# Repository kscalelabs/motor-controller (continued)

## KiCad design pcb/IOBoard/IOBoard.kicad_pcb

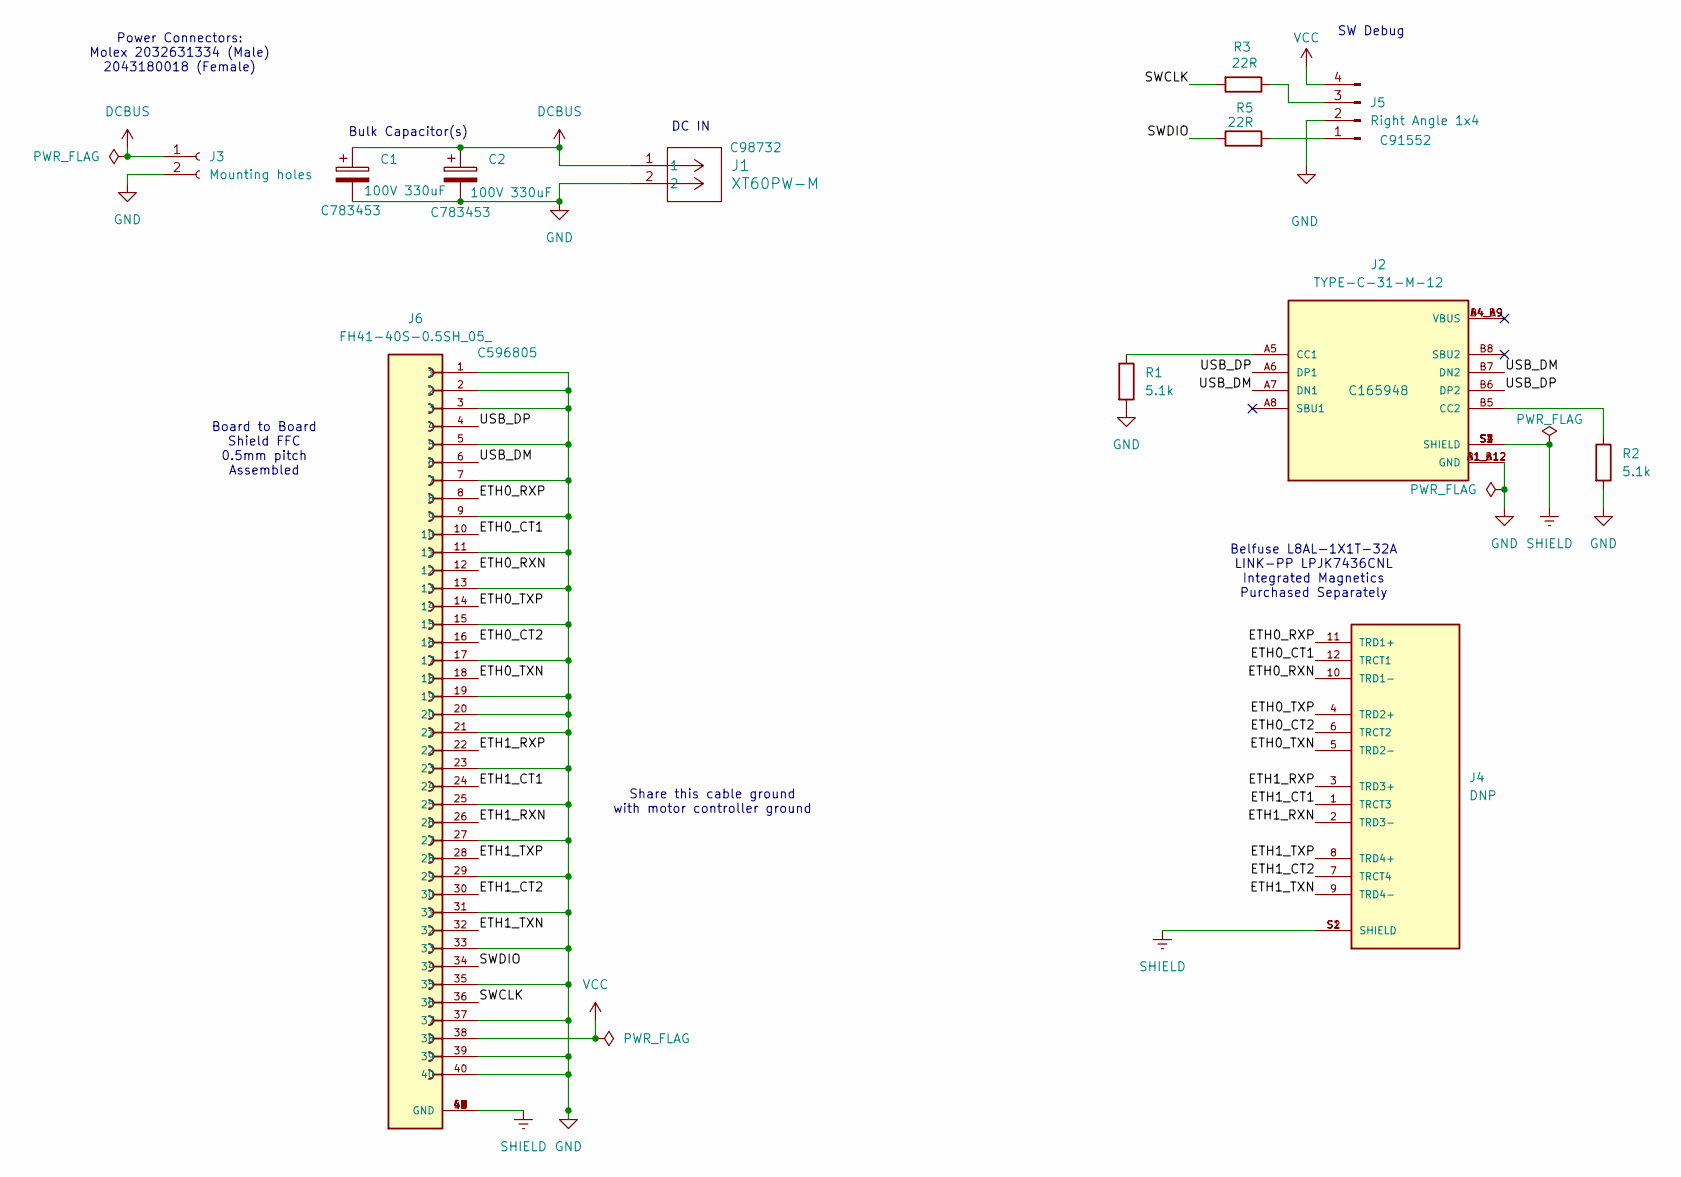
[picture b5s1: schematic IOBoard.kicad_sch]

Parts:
C1, C2: 100V 330uF; CP_Radial_D13.0mm_P5.00mm; LCSC Part Number C783453
J1: XT60PW-M; CONN_XT60PW-M_AMA; LCSC Part Number C98732
J2: TYPE-C-31-M-12; HRO_TYPE-C-31-M-12; PARTREV 2020.12.08; LCSC Part Number C165948
J3: Mounting holes; Dual Post
J4: DNP; BEL_L8AL-1X1T-32A; PARTREV A; LCSC Part Number LINK-PP LPJK7436CNL
J5: Right Angle 1x4; PinHeader_1x04_P2.54mm_Horizontal; LCSC Part Number C91552
J6: FH41-40S-0.5SH_05_; HRS_FH41-40S-0.5SH_05_; PARTREV 18.03.19; LCSC Part Number C596805
R1, R2: 5.1k; R_0603_1608Metric
R3, R5: 22R; R_0603_1608Metric; TOLERANCE ±1%; MANUFACTURER PART NUMBER RC0603FR-0722RL

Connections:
/ETH0_CT1: J4.12 (TRCT1), J6.10
/ETH0_CT2: J4.6 (TRCT2), J6.16
/ETH0_RXN: J4.10 (TRD1-), J6.12
/ETH0_RXP: J4.11 (TRD1+), J6.8
/ETH0_TXN: J4.5 (TRD2-), J6.18
/ETH0_TXP: J4.4 (TRD2+), J6.14
/ETH1_CT1: J4.1 (TRCT3), J6.24
/ETH1_CT2: J4.7 (TRCT4), J6.30
/ETH1_RXN: J4.2 (TRD3-), J6.26
/ETH1_RXP: J4.3 (TRD3+), J6.22
/ETH1_TXN: J4.9 (TRD4-), J6.32
/ETH1_TXP: J4.8 (TRD4+), J6.28
/SWCLK: J6.36, R3.2
/SWDIO: J6.34, R5.1
/USB_DM: J2.A7 (DN1), J2.B7 (DN2), J6.6
/USB_DP: J2.A6 (DP1), J2.B6 (DP2), J6.4
DCBUS: C1.1, C2.1, J1.1, J3.1
GND: C1.2, C2.2, J1.2, J2.A1_B12 (GND), J2.B1_A12 (GND), J3.2, J5.2, J6.1, J6.2, J6.3, J6.5, J6.7, J6.9, J6.11, J6.13, J6.15, J6.17, J6.19, J6.20, J6.21, J6.23, J6.25, J6.27, J6.29, J6.31, J6.33, J6.35, J6.37, J6.39, J6.40, R1.2, R2.2
unnamed: J2.A5 (CC1), R1.1
unnamed: J2.B5 (CC2), R2.1
unnamed: J5.1, R5.2
unnamed: J5.3, R3.1
SHIELD: J2.S1 (SHIELD), J2.S2 (SHIELD), J2.S3 (SHIELD), J2.S4 (SHIELD), J4.S1 (SHIELD), J4.S2 (SHIELD), J6.41 (GND), J6.42 (GND), J6.43 (GND), J6.44 (GND), J6.45 (GND), J6.46 (GND), J6.47 (GND), J6.48 (GND), J6.49 (GND), J6.50 (GND)
VCC: J5.4, J6.38

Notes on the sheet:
Belfuse L8AL-1X1T-32A LINK-PP LPJK7436CNL Integrated Magnetics Purchased Separately
SW Debug
Board to Board Shield FFC 0.5mm pitch Assembled
Share this cable ground with motor controller ground
DC IN
Power Connectors: Molex 2032631334 (Male) 2043180018 (Female)
Bulk Capacitor(s)

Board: 4 copper layers, 12 parts (0 on the bottom side), 24 nets, no tracks yet.

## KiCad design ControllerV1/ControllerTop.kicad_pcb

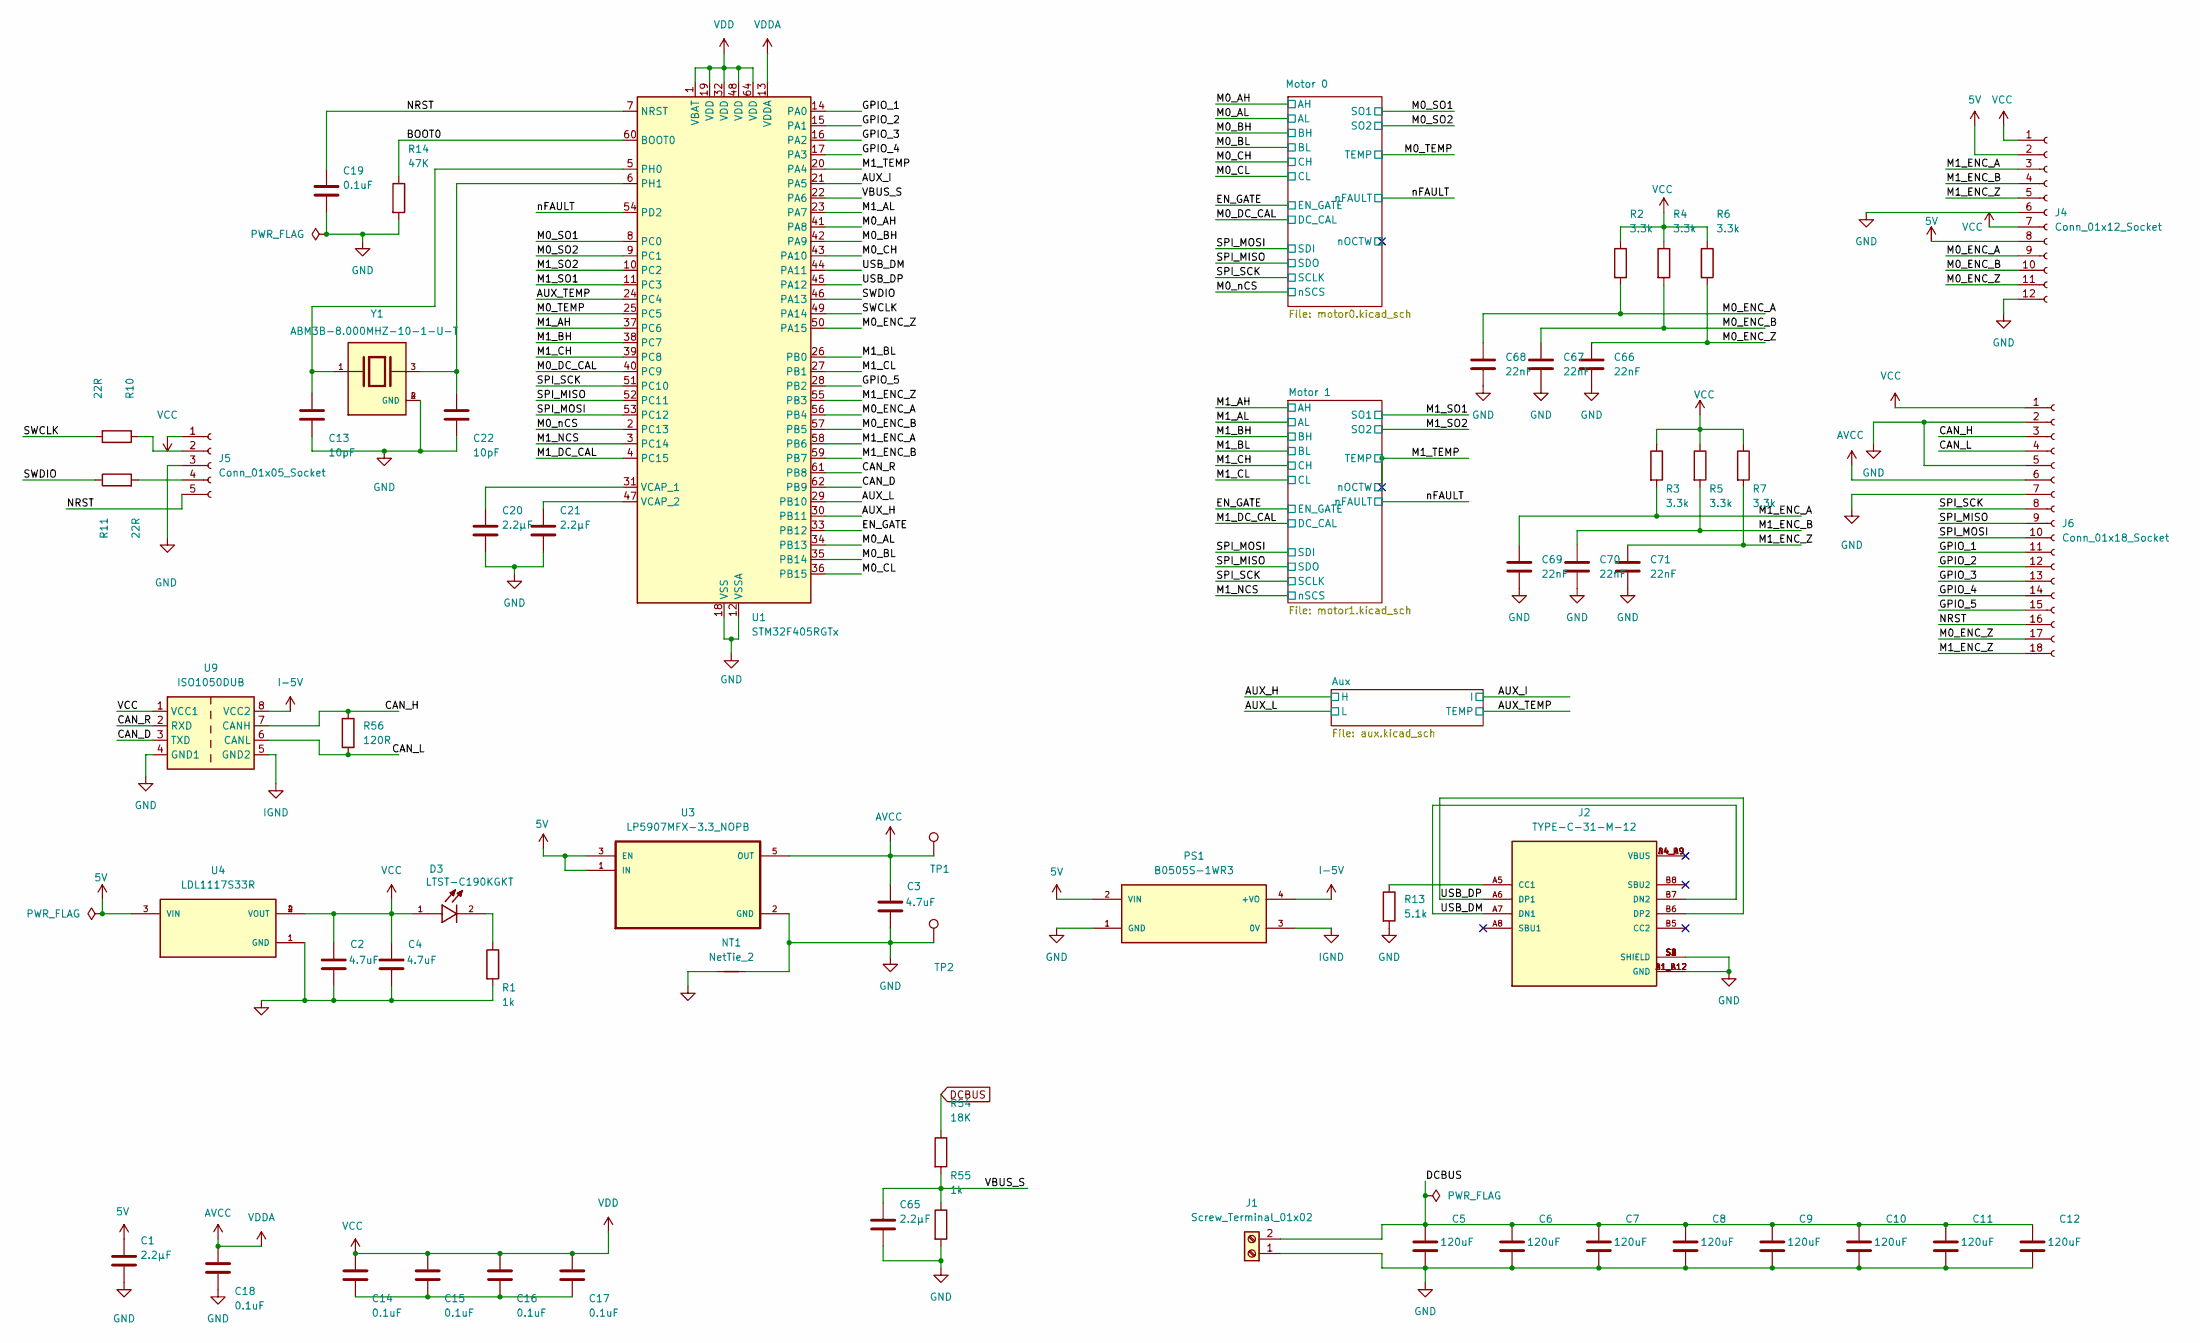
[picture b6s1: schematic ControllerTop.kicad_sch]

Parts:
C1, C20, C21, C65: 2.2µF; C_0603_1608Metric; TOLERANCE ±10%; VOLTAGE - RATED 16V; MANUFACTURER PART NUMBER GRM188R61C225KE15D
C2, C3, C4: 4.7uF; C_0805_2012Metric; TOLERANCE ±10%; VOLTAGE - RATED 35V; PART STATUS Active
C5, C6, C7, C8, C9, C10, C11, C12: 470uF; C_Elec_10x10.2; TOLERANCE ±20%; PART STATUS Active
C13, C22: 10pF; C_0603_1608Metric; TOLERANCE ±5%; VOLTAGE - RATED 50V; MANUFACTURER PART NUMBER GRM1885C1H100JA01D
C14, C15, C16, C17, C18, C19: 0.1uF; C_0603_1608Metric; TOLERANCE ±10%; VOLTAGE - RATED 50V; MANUFACTURER PART NUMBER GRM188R71H104KA93D
C66, C67, C68, C69, C70, C71: 22nF; C_0402_1005Metric
D3: LTST-C190KGKT; D_0603_1608Metric
J1: Screw_Terminal_01x02; TerminalBlock_MetzConnect_Type011_RT05502HBWC_1x02_P5.00mm_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
J2: TYPE-C-31-M-12; HRO_TYPE-C-31-M-12; PARTREV 2020.12.08
J4: Conn_01x12_Socket; PinSocket_1x12_P2.54mm_Vertical
J5: Conn_01x05_Socket; PinSocket_1x05_P2.54mm_Vertical
J6: Conn_01x18_Socket; PinSocket_1x18_P2.54mm_Vertical
NT1: NetTie_2; NetTie-2_SMD_Pad0.5mm
PS1: B0505S-1WR3; R_Array_SIP4; PARTREV 2018.06.29-A/2
R1, R55: 1k; R_0603_1608Metric; TOLERANCE ±1%; MANUFACTURER PART NUMBER RC0603FR-071KL
R2, R3, R4, R5, R6, R7: 3.3k; R_0603_1608Metric; TOLERANCE ±1%; MANUFACTURER PART NUMBER RC0603FR-073K3L
R10, R11: 22R; R_0603_1608Metric; TOLERANCE ±1%; MANUFACTURER PART NUMBER RC0603FR-0722RL
R13: 5.1k; R_0603_1608Metric
R14: 47K; R_0603_1608Metric; TOLERANCE ±1%; MANUFACTURER PART NUMBER RC0603FR-0747KL
R54: 18K; R_0603_1608Metric; TOLERANCE ±1%; MANUFACTURER PART NUMBER RC0603FR-0710KL
R56: 120R; R_0603_1608Metric
TP1, TP2: TESTPOINT; TestPoint_Pad_1.0x1.0mm
U1: STM32F405RGTx; LQFP-64_10x10mm_P0.5mm
U3: LP5907MFX-3.3_NOPB; SOT-23-5
U4: LDL1117S33R; SOT-223; PARTREV 7
U9: ISO1050DUB; SOP-8_6.62x9.15mm_P2.54mm
Y1: ABM3B-8.000MHZ-10-1-U-T; Crystal_SMD_5032-4Pin_5.0x3.2mm; PARTREV 08.25.15

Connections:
5V: C1.1, J4.2, J4.8, PS1.2 (VIN), U3.1 (IN), U3.3 (EN), U4.3 (VIN); also elsewhere on the board
/AUX_H: U1.30 (PB11); also elsewhere on the board
/AUX_I: U1.21 (PA5); also elsewhere on the board
/AUX_L: U1.29 (PB10); also elsewhere on the board
/AUX_TEMP: U1.24 (PC4); also elsewhere on the board
/BOOT0: R14.1, U1.60 (BOOT0)
/CAN_D: U1.62 (PB9), U9.3 (TXD)
/CAN_H: J6.3, R56.1, U9.7 (CANH)
/CAN_L: J6.4, R56.2, U9.6 (CANL)
/CAN_R: U1.61 (PB8), U9.2 (RXD)
/EN_GATE: U1.33 (PB12); also elsewhere on the board
/GPIO_1: J6.11, U1.14 (PA0)
/GPIO_2: J6.12, U1.15 (PA1)
/GPIO_3: J6.13, U1.16 (PA2)
/GPIO_4: J6.14, U1.17 (PA3)
/GPIO_5: J6.15, U1.28 (PB2)
/M0_AH: U1.41 (PA8); also elsewhere on the board
/M0_AL: U1.34 (PB13); also elsewhere on the board
/M0_BH: U1.42 (PA9); also elsewhere on the board
/M0_BL: U1.35 (PB14); also elsewhere on the board
/M0_CH: U1.43 (PA10); also elsewhere on the board
/M0_CL: U1.36 (PB15); also elsewhere on the board
/M0_DC_CAL: U1.40 (PC9); also elsewhere on the board
/M0_ENC_A: C68.1, J4.9, R2.2, U1.56 (PB4)
/M0_ENC_B: C67.1, J4.10, R4.2, U1.57 (PB5)
/M0_ENC_Z: C66.1, J4.11, J6.17, R6.2, U1.50 (PA15)
/M0_SO1: U1.8 (PC0); also elsewhere on the board
/M0_SO2: U1.9 (PC1); also elsewhere on the board
/M0_TEMP: U1.25 (PC5); also elsewhere on the board
/M0_nCS: U1.2 (PC13); also elsewhere on the board
/M1_AH: U1.37 (PC6); also elsewhere on the board
/M1_AL: U1.23 (PA7); also elsewhere on the board
/M1_BH: U1.38 (PC7); also elsewhere on the board
/M1_BL: U1.26 (PB0); also elsewhere on the board
/M1_CH: U1.39 (PC8); also elsewhere on the board
/M1_CL: U1.27 (PB1); also elsewhere on the board
/M1_DC_CAL: U1.4 (PC15); also elsewhere on the board
/M1_ENC_A: C69.1, J4.3, R3.2, U1.58 (PB6)
/M1_ENC_B: C70.1, J4.4, R5.2, U1.59 (PB7)
/M1_ENC_Z: C71.1, J4.5, J6.18, R7.2, U1.55 (PB3)
/M1_NCS: U1.3 (PC14); also elsewhere on the board
/M1_SO1: U1.11 (PC3); also elsewhere on the board
/M1_SO2: U1.10 (PC2); also elsewhere on the board
/M1_TEMP: U1.20 (PA4); also elsewhere on the board
/NRST: C19.1, J5.5, J6.16, U1.7 (NRST)
/SPI_MISO: J6.9, U1.52 (PC11); also elsewhere on the board
/SPI_MOSI: J6.10, U1.53 (PC12); also elsewhere on the board
/SPI_SCK: J6.8, U1.51 (PC10); also elsewhere on the board
/SWCLK: R10.2, U1.49 (PA14)
/SWDIO: R11.1, U1.46 (PA13)
/USB_DM: J2.A7 (DN1), J2.B7 (DN2), U1.44 (PA11)
/USB_DP: J2.A6 (DP1), J2.B6 (DP2), U1.45 (PA12)
/VBUS_S: C65.1, R54.2, R55.1, U1.22 (PA6)
/nFAULT: U1.54 (PD2); also elsewhere on the board
AVCC: C3.1, C18.1, J6.6, TP1.1, U1.13 (VDDA), U3.5 (OUT); also elsewhere on the board
DCBUS: C5.1, C6.1, C7.1, C8.1, C9.1, C10.1, C11.1, C12.1, J1.2, R54.1; also elsewhere on the board
GND: C1.2, C2.2, C3.2, C4.2, C5.2, C6.2, C7.2, C8.2, C9.2, C10.2, C11.2, C12.2, C13.2, C18.2, C19.2, C20.2, C21.2, C22.2, C65.2, C66.2, C67.2, C68.2, C69.2, C70.2, C71.2, J1.1, J2.A1_B12 (GND), J2.B1_A12 (GND), J2.S1 (SHIELD), J2.S2 (SHIELD), J2.S3 (SHIELD), J2.S4 (SHIELD), J4.6, J4.12, J5.3, J6.2, J6.5, J6.7, NT1.1, NT1.2, PS1.1 (GND), R1.2, R13.2, R14.2, R55.2, TP2.1, U1.12 (VSSA), U1.18 (VSS), U1.63 (VSS), U3.2 (GND), U4.1 (GND), U9.4 (GND1), Y1.2 (GND), Y1.4 (GND); also elsewhere on the board
I-5V: PS1.4 (+VO), U9.8 (VCC2)
IGND: PS1.3 (0V), U9.5 (GND2)
unnamed: C14.2, C15.2, C16.2, C17.2
unnamed: D3.2, R1.1
unnamed: J2.A5 (CC1), R13.1
unnamed: J5.2, R10.1
unnamed: J5.4, R11.2
unnamed: C13.1, U1.5 (PH0), Y1.1
unnamed: C22.1, U1.6 (PH1), Y1.3
unnamed: C20.1, U1.31 (VCAP_1)
unnamed: C21.1, U1.47 (VCAP_2)
VCC: C2.1, C4.1, C14.1, C15.1, C16.1, C17.1, D3.1, J4.1, J4.7, J5.1, J6.1, R2.1, R3.1, R4.1, R5.1, R6.1, R7.1, U1.1 (VBAT), U1.19 (VDD), U1.32 (VDD), U1.48 (VDD), U1.64 (VDD), U4.2 (VOUT), U4.4 (VOUT), U9.1 (VCC1); also elsewhere on the board

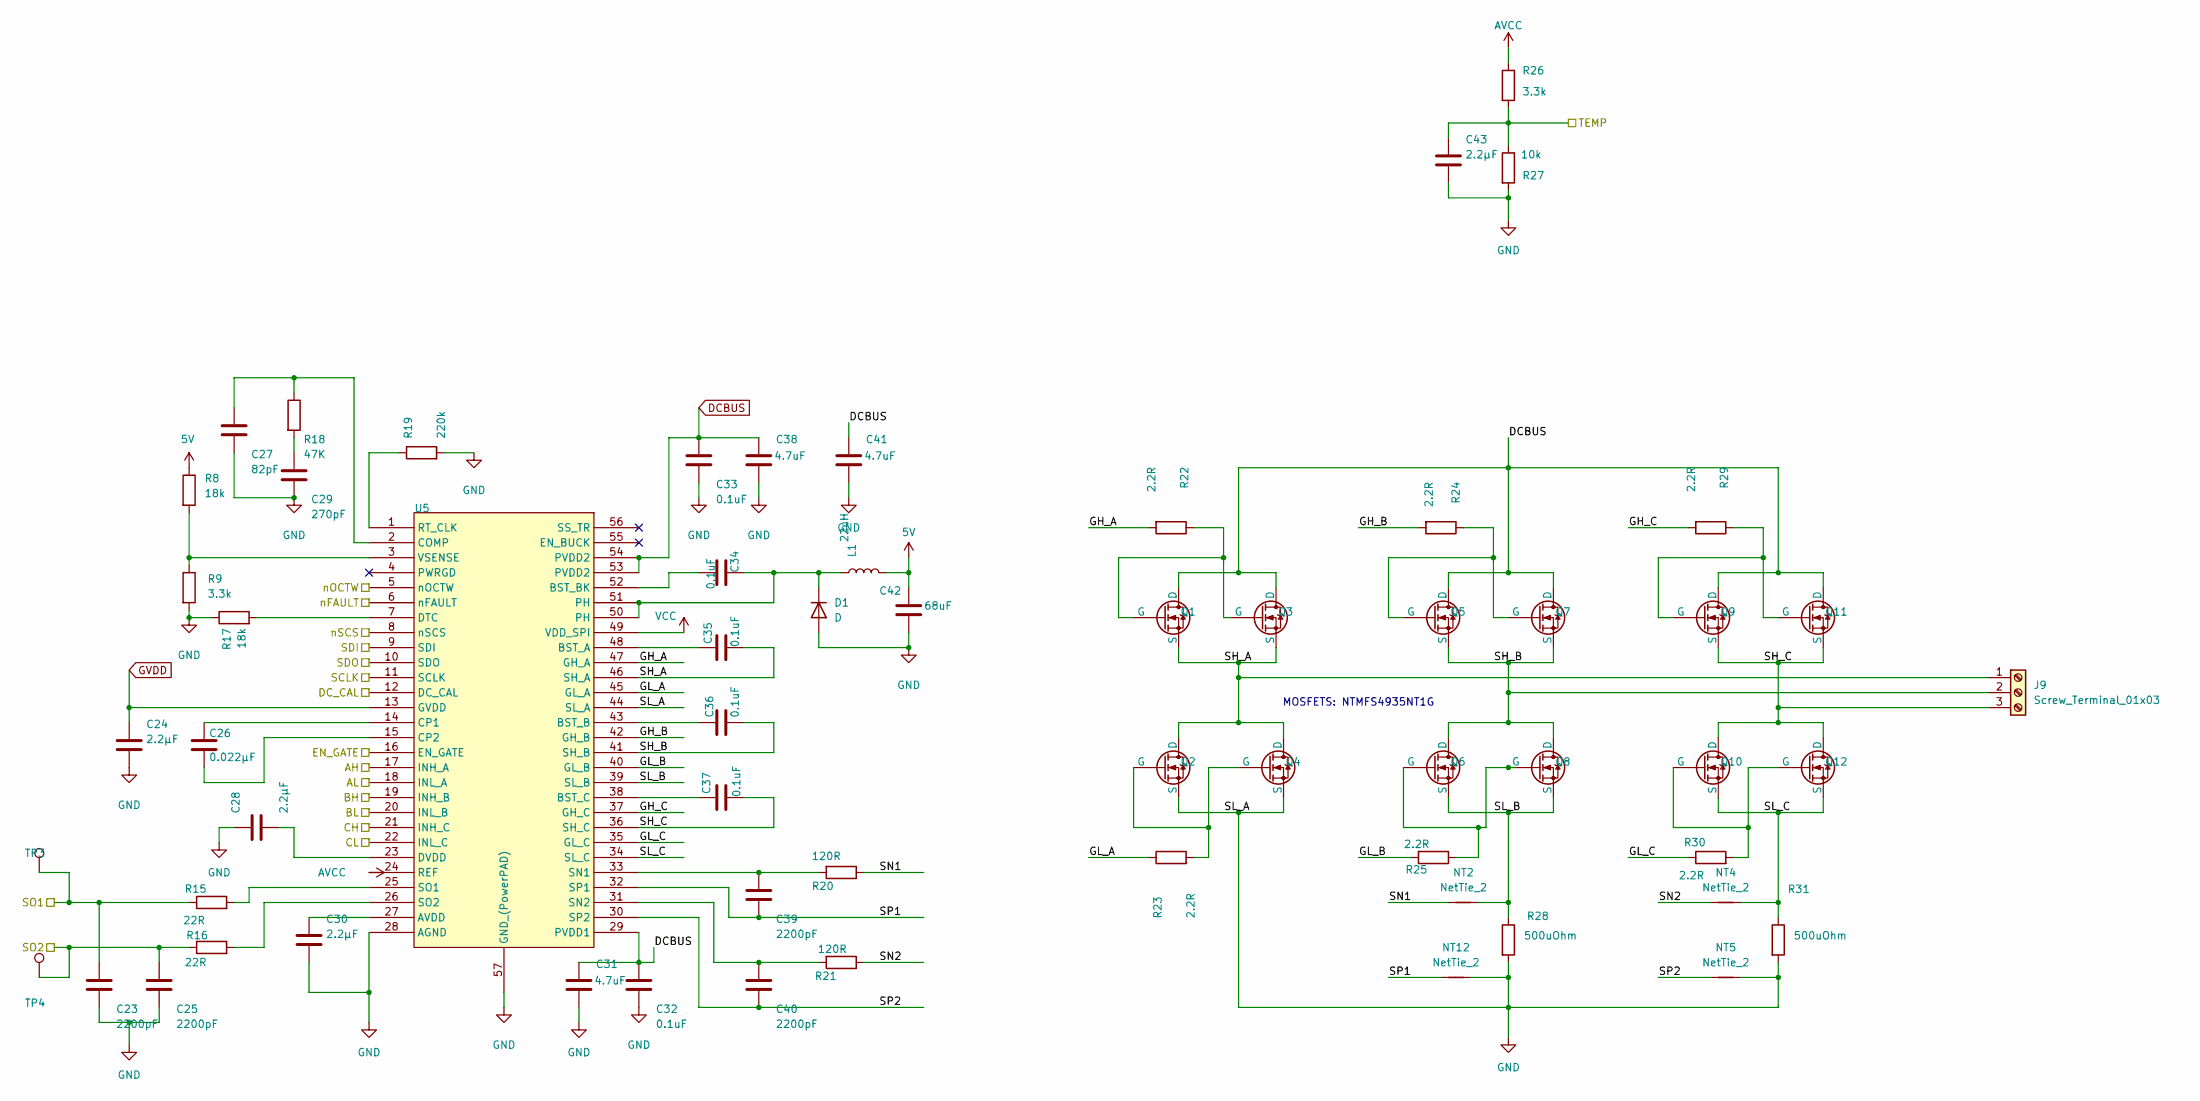
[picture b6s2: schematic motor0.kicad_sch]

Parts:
C23, C25, C39, C40: 2200pF; C_0603_1608Metric; TOLERANCE ±5%; VOLTAGE - RATED 50V; PART STATUS Active
C24, C28, C30, C43: 2.2µF; C_0603_1608Metric; TOLERANCE ±10%; VOLTAGE - RATED 16V; MANUFACTURER PART NUMBER GRM188R61C225KE15D
C26: 0.022µF; C_0603_1608Metric; TOLERANCE ±10%; VOLTAGE - RATED 50V; MANUFACTURER PART NUMBER GRM188R71H223KA01D
C27: 82pF; C_0603_1608Metric; TOLERANCE ±5%; VOLTAGE - RATED 100V; MANUFACTURER PART NUMBER GRM1885C2A820JA01D
C29: 270pF; C_0603_1608Metric; TOLERANCE ±5%; VOLTAGE - RATED 50V; MANUFACTURER PART NUMBER GRM1885C1H271JA01D
C31, C38, C41: 4.7uF; C_0805_2012Metric; TOLERANCE ±10%; VOLTAGE - RATED 35V; PART STATUS Active
C32, C33, C34, C35, C36, C37: 0.1uF; C_0603_1608Metric; TOLERANCE ±10%; VOLTAGE - RATED 50V; MANUFACTURER PART NUMBER GRM188R71H104KA93D
C42: 68uF; CP_EIA-6032-28_Kemet-C; TOLERANCE ±20%; PART STATUS Active
D1: D; D_SOD-123F
J9: Screw_Terminal_01x03; TerminalBlock_MetzConnect_Type011_RT05503HBWC_1x03_P5.00mm_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
L1: 22uH; L_Taiyo-Yuden_NR-60xx
NT2, NT4, NT5, NT12: NetTie_2; NetTie-2_SMD_Pad0.5mm
Q1, Q2, Q3, Q4, Q5, Q6, Q8, Q9, Q10, Q12: ONSemi_SO-8FL_488AA; DRIVE VOLTAGE (MAX RDS 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 4.5V, 10V; PART STATUS Active
Q7, Q11: FILL_FOOTPRINT; ONSemi_SO-8FL_488AA; DRIVE VOLTAGE (MAX RDS 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 4.5V, 10V; PART STATUS Active
R8, R17: 18k; R_0603_1608Metric; TOLERANCE ±1%; MANUFACTURER PART NUMBER RC0603FR-0718KL
R9, R26: 3.3k; R_0603_1608Metric; TOLERANCE ±1%; MANUFACTURER PART NUMBER RC0603FR-073K3L
R15, R16: 22R; R_0603_1608Metric; TOLERANCE ±1%; MANUFACTURER PART NUMBER RC0603FR-0722RL
R18: 47K; R_0603_1608Metric; TOLERANCE ±1%; MANUFACTURER PART NUMBER RC0603FR-0747KL
R19: 220k; R_0603_1608Metric; TOLERANCE ±1%; MANUFACTURER PART NUMBER RC0603FR-07220KL
R20, R21: 120R; R_0603_1608Metric; TOLERANCE ±1%; MANUFACTURER PART NUMBER RC0603FR-07120RL
R22, R23, R24, R25, R29, R30: 2.2R; R_0603_1608Metric; TOLERANCE ±1%; MANUFACTURER PART NUMBER RC0603FR-072R2L
R27: 10k; R_0402_1005Metric
R28, R31: 500uOhm; R_2512_6332Metric; TOLERANCE ±1%; PART STATUS Active
TP3, TP4: TESTPOINT; TestPoint_Pad_1.0x1.0mm
U5: HTSSOP-56-1EP_6.1x14mm_P0.5mm_EP3.61x6.35mm

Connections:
5V: C42.1, L1.2, R8.1; also elsewhere on the board
/EN_GATE: U5.16 (EN_GATE); also elsewhere on the board
/M0_AH: U5.17 (INH_A); also elsewhere on the board
/M0_AL: U5.18 (INL_A); also elsewhere on the board
/M0_BH: U5.19 (INH_B); also elsewhere on the board
/M0_BL: U5.20 (INL_B); also elsewhere on the board
/M0_CH: U5.21 (INH_C); also elsewhere on the board
/M0_CL: U5.22 (INL_C); also elsewhere on the board
/M0_DC_CAL: U5.12 (DC_CAL); also elsewhere on the board
/M0_SO1: C23.1, R15.1, TP3.1; also elsewhere on the board
/M0_SO2: C25.1, R16.1, TP4.1; also elsewhere on the board
/M0_TEMP: C43.1, R26.2, R27.1; also elsewhere on the board
/M0_nCS: U5.8 (nSCS); also elsewhere on the board
/Motor 0/GH_A: R22.2, U5.47 (GH_A)
/Motor 0/GH_B: R24.2, U5.42 (GH_B)
/Motor 0/GH_C: R29.2, U5.37 (GH_C)
/Motor 0/GL_A: R23.1, U5.45 (GL_A)
/Motor 0/GL_B: R25.2, U5.40 (GL_B)
/Motor 0/GL_C: R30.1, U5.35 (GL_C)
/Motor 0/SH_A: C35.2, J9.1, Q1.1 (S), Q2.5 (D), Q3.1 (S), Q4.5 (D), U5.46 (SH_A)
/Motor 0/SH_B: C36.2, J9.2, Q5.1 (S), Q6.5 (D), Q7.1 (S), Q8.5 (D), U5.41 (SH_B)
/Motor 0/SH_C: C37.2, J9.3, Q9.1 (S), Q10.5 (D), Q11.1 (S), Q12.5 (D), U5.36 (SH_C)
/Motor 0/SL_B: NT2.2, Q6.1 (S), Q8.1 (S), R28.1, U5.39 (SL_B)
/Motor 0/SL_C: NT4.2, Q10.1 (S), Q12.1 (S), R31.1, U5.34 (SL_C)
/Motor 0/SN1: NT2.1, R20.1
/Motor 0/SN2: NT4.1, R21.1
/Motor 0/SP1: C39.2, NT12.1, U5.32 (SP1)
/Motor 0/SP2: C40.2, NT5.1, U5.30 (SP2)
/Motor 0/nOCTW: U5.5 (nOCTW)
/SPI_MISO: U5.10 (SDO); also elsewhere on the board
/SPI_MOSI: U5.9 (SDI); also elsewhere on the board
/SPI_SCK: U5.11 (SCLK); also elsewhere on the board
/nFAULT: U5.6 (nFAULT); also elsewhere on the board
AVCC: R26.1, U5.24 (REF); also elsewhere on the board
DCBUS: C31.1, C32.1, C33.1, C38.1, C41.1, Q1.5 (D), Q3.5 (D), Q5.5 (D), Q7.5 (D), Q9.5 (D), Q11.5 (D), U5.29 (PVDD1), U5.53 (PVDD2), U5.54 (PVDD2); also elsewhere on the board
GND: C23.2, C24.2, C25.2, C27.2, C28.1, C29.2, C30.2, C31.2, C32.2, C33.2, C38.2, C41.2, C42.2, C43.2, D1.2 (A), NT5.2, NT12.2, Q2.1 (S), Q4.1 (S), R9.2, R17.1, R19.2, R27.2, R28.2, R31.2, U5.28 (AGND), U5.44 (SL_A), U5.57 (GND_(PowerPAD)); also elsewhere on the board
GVDD: C24.1, U5.13 (GVDD); also elsewhere on the board
unnamed: C29.1, R18.2
unnamed: C34.1, D1.1 (K), L1.1, U5.50 (PH), U5.51 (PH)
unnamed: Q1.4 (G), Q3.4 (G), R22.1
unnamed: Q2.4 (G), Q4.4 (G), R23.2
unnamed: Q5.4 (G), Q7.4 (G), R24.1
unnamed: Q6.4 (G), Q8.4 (G), R25.1
unnamed: Q10.4 (G), Q12.4 (G), R30.2
unnamed: Q9.4 (G), Q11.4 (G), R29.1
unnamed: C30.1, U5.27 (AVDD)
unnamed: C35.1, U5.48 (BST_A)
unnamed: C36.1, U5.43 (BST_B)
unnamed: C34.2, U5.52 (BST_BK)
unnamed: C37.1, U5.38 (BST_C)
unnamed: C27.1, R18.1, U5.2 (COMP)
unnamed: C26.1, U5.14 (CP1)
unnamed: C26.2, U5.15 (CP2)
unnamed: R17.2, U5.7 (DTC)
unnamed: C28.2, U5.23 (DVDD)
unnamed: R19.1, U5.1 (RT_CLK)
unnamed: C39.1, R20.2, U5.33 (SN1)
unnamed: C40.1, R21.2, U5.31 (SN2)
unnamed: R15.2, U5.25 (SO1)
unnamed: R16.2, U5.26 (SO2)
unnamed: R8.2, R9.1, U5.3 (VSENSE)
VCC: U5.49 (VDD_SPI); also elsewhere on the board

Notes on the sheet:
MOSFETS: NTMFS4935NT1G

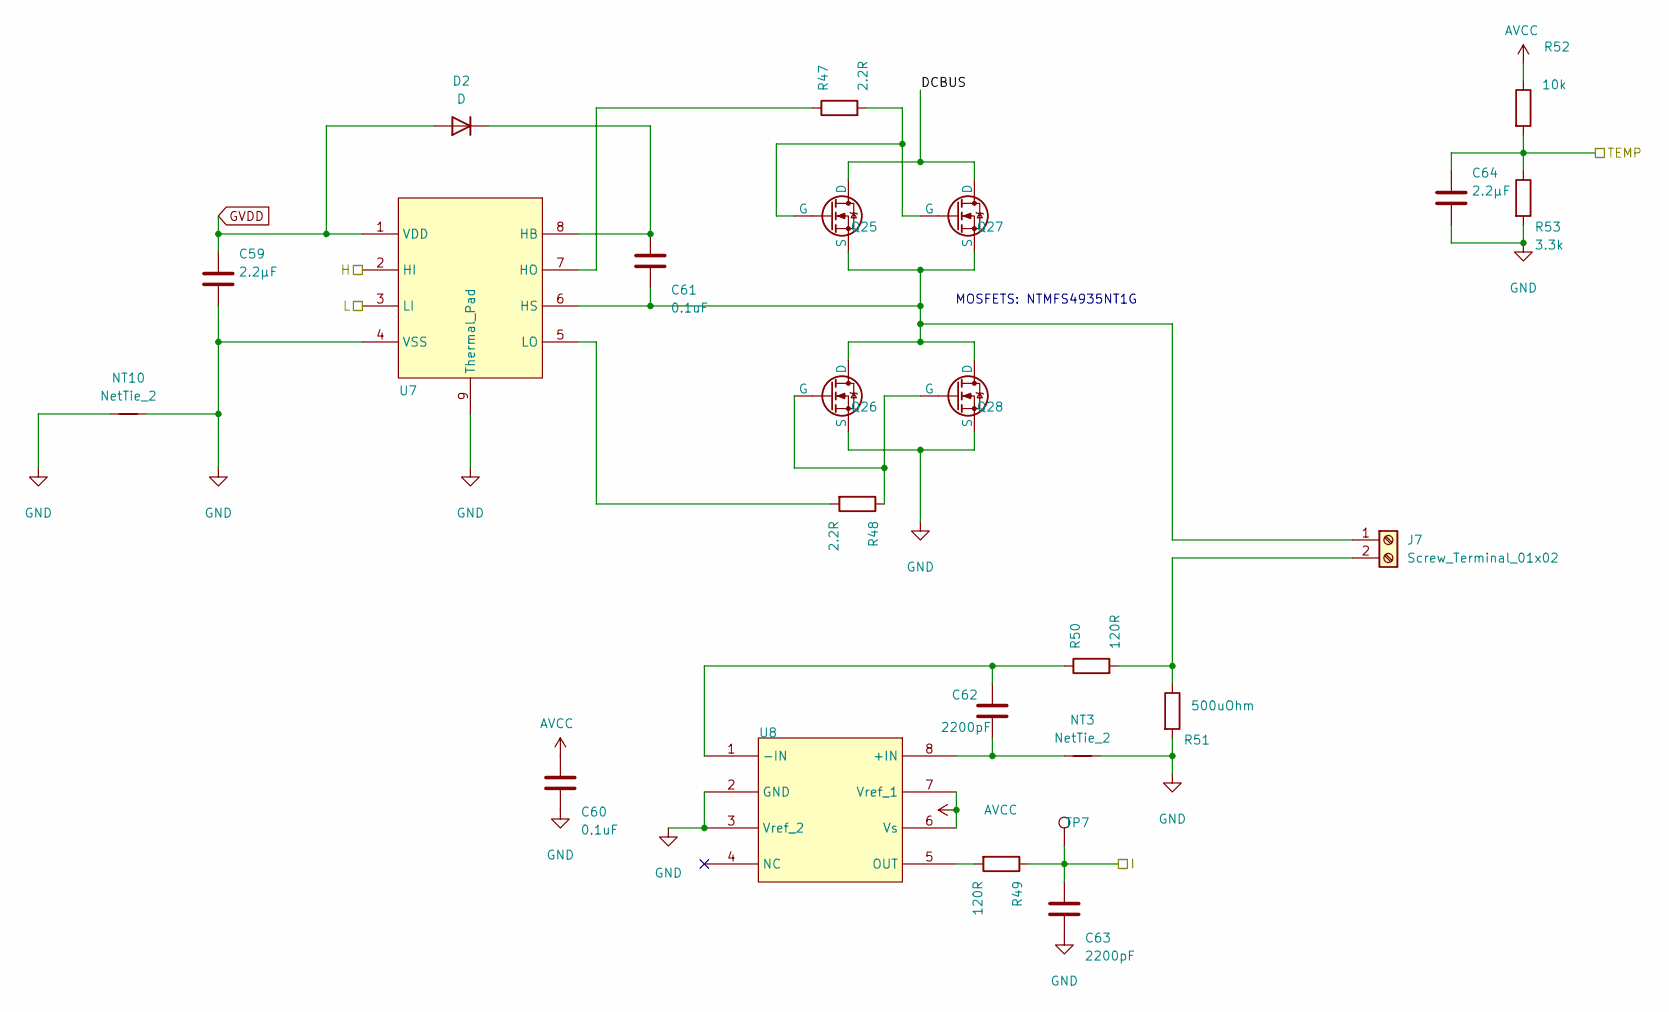
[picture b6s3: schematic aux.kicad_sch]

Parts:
C59, C64: 2.2µF; C_0603_1608Metric; TOLERANCE ±10%; VOLTAGE - RATED 16V; MANUFACTURER PART NUMBER GRM188R61C225KE15D
C60, C61: 0.1uF; C_0603_1608Metric; TOLERANCE ±10%; VOLTAGE - RATED 50V; MANUFACTURER PART NUMBER GRM188R71H104KA93D
C62, C63: 2200pF; C_0603_1608Metric; TOLERANCE ±5%; VOLTAGE - RATED 50V; PART STATUS Active
D2: D; D_SOD-123F
J7: Screw_Terminal_01x02; TerminalBlock_MetzConnect_Type011_RT05502HBWC_1x02_P5.00mm_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
NT3, NT10: NetTie_2; NetTie-2_SMD_Pad0.5mm
Q25: FILL_FOOTPRINT; ONSemi_SO-8FL_488AA; DRIVE VOLTAGE (MAX RDS 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 4.5V, 10V; PART STATUS Active
Q26, Q27, Q28: ONSemi_SO-8FL_488AA; DRIVE VOLTAGE (MAX RDS 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 4.5V, 10V; PART STATUS Active
R47, R48: 2.2R; R_0603_1608Metric; TOLERANCE ±1%; MANUFACTURER PART NUMBER RC0603FR-072R2L
R49, R50: 120R; R_0603_1608Metric; TOLERANCE ±1%; MANUFACTURER PART NUMBER RC0603FR-07120RL
R51: 500uOhm; R_2512_6332Metric; TOLERANCE ±1%; PART STATUS Active
R52: 10k; R_0402_1005Metric
R53: 3.3k; R_0603_1608Metric; TOLERANCE ±1%; MANUFACTURER PART NUMBER RC0603FR-073K3L
TP7: TESTPOINT; TestPoint_Pad_1.0x1.0mm
U7: WSON-8-1EP_4x4mm_P0.8mm_EP2.6x3mm
U8: SOIC-8_3.9x4.9mm_P1.27mm

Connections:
/AUX_H: U7.2 (HI); also elsewhere on the board
/AUX_I: C63.1, R49.1, TP7.1; also elsewhere on the board
/AUX_L: U7.3 (LI); also elsewhere on the board
/AUX_TEMP: C64.1, R52.2, R53.1; also elsewhere on the board
/Aux/DCBUS: Q25.5 (D), Q27.5 (D)
AVCC: C60.1, R52.1, U8.6 (Vs), U8.7 (Vref_1); also elsewhere on the board
GND: C59.2, C60.2, C63.2, C64.2, NT3.2, NT10.1, NT10.2, Q26.1 (S), Q28.1 (S), R51.2, R53.2, U7.4 (VSS), U7.9 (Thermal_Pad), U8.2 (GND), U8.3 (Vref_2); also elsewhere on the board
GVDD: C59.1, D2.2 (A), U7.1 (VDD); also elsewhere on the board
unnamed: C61.1, D2.1 (K), U7.8 (HB)
unnamed: C61.2, J7.1, Q25.1 (S), Q26.5 (D), Q27.1 (S), Q28.5 (D), U7.6 (HS)
unnamed: J7.2, R50.2, R51.1
unnamed: Q25.4 (G), Q27.4 (G), R47.2
unnamed: Q26.4 (G), Q28.4 (G), R48.1
unnamed: R47.1, U7.7 (HO)
unnamed: R48.2, U7.5 (LO)
unnamed: C62.2, NT3.1, U8.8 (+IN)
unnamed: C62.1, R50.1, U8.1 (-IN)
unnamed: R49.2, U8.5 (OUT)

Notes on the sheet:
MOSFETS: NTMFS4935NT1G
